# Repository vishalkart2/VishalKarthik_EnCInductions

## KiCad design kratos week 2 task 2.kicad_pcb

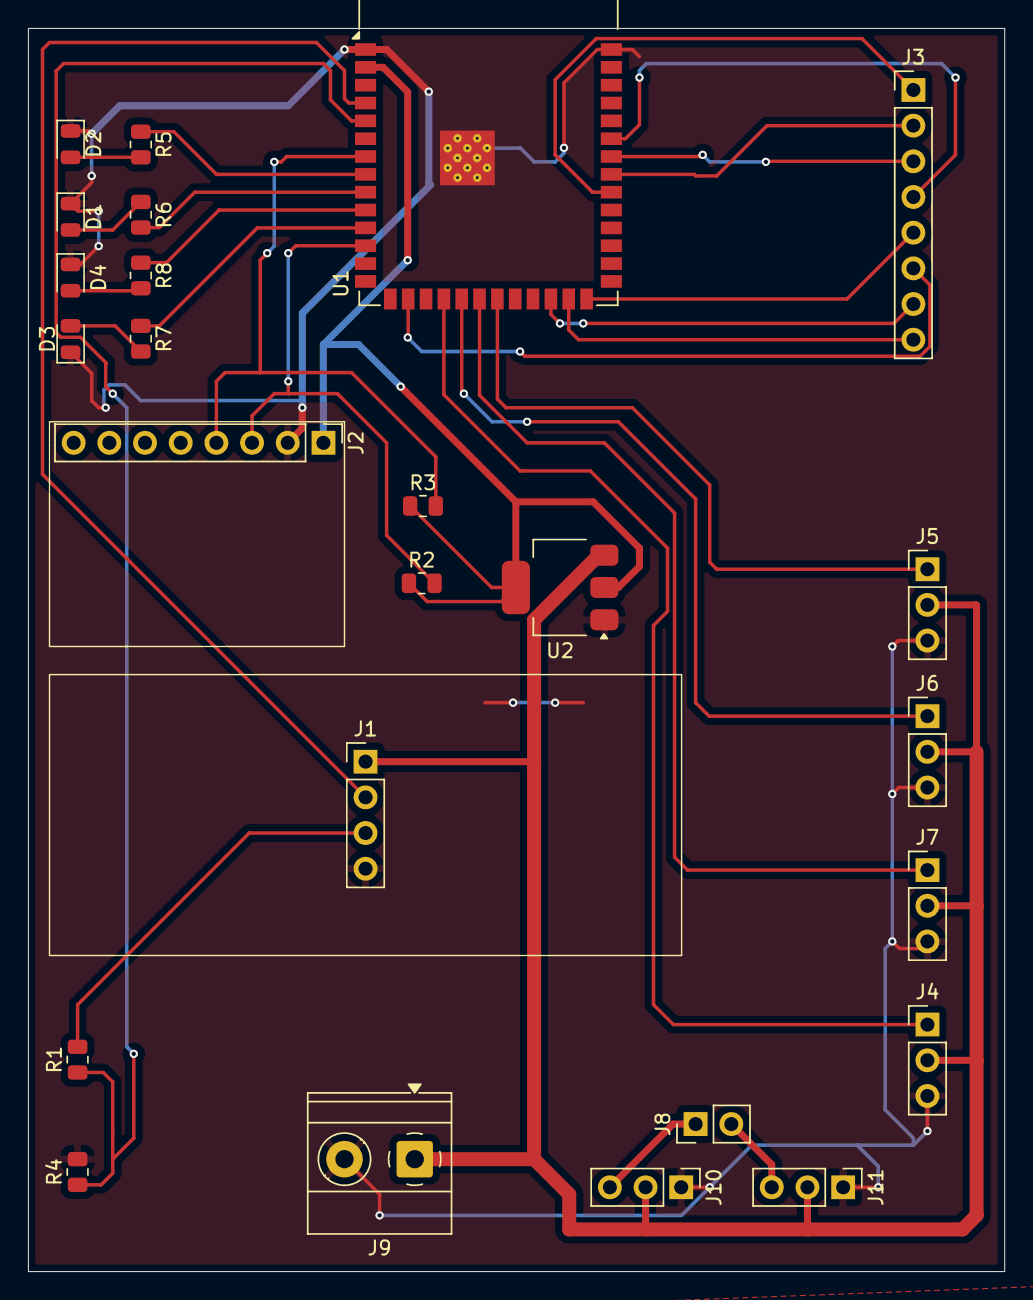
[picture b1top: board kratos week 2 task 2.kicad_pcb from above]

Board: 2 copper layers, 69.5 x 88.5 mm, 25 parts (0 on the bottom side), 30 nets.

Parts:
D1, D2, D3, D4: LED; LED_0805_2012Metric
J1: Conn_01x04; PinHeader_1x04_P2.54mm_Vertical
J2, J3: Conn_01x08; PinHeader_1x08_P2.54mm_Vertical
J4, J5, J6, J7: Conn_01x03; PinHeader_1x03_P2.54mm_Vertical
J8: Conn_01x02; PinHeader_1x02_P2.54mm_Vertical
J9: Conn_01x02; TerminalBlock_Phoenix_MKDS-1,5-2_1x02_P5.00mm_Horizontal
J10: Conn_01x03 - SWITCH 1; PinHeader_1x03_P2.54mm_Vertical
J11: Conn_01x03 - SWITCH 2; PinHeader_1x03_P2.54mm_Vertical
R1: 1000R; R_0805_2012Metric
R2, R3: 4700R; R_0805_2012Metric
R4: 2000R; R_0805_2012Metric
R5, R6, R7, R8: 220R; R_0805_2012Metric
U1: ESP32-S3-WROOM-1
U2: AMS1117-3.3; SOT-223-3_TabPin2

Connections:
+3.3V: J2.1, R2.1, R3.1, U1.2 (3V3), U2.2 (VO)
/+5V: J1.1, J4.2, J5.2, J6.2, J7.2, J9.1, J10.2, J11.2, U2.3 (VI)
/ECHO: R1.1, R4.1, U1.5 (IO5)
/GND: D1.1 (K), D2.1 (K), D3.1 (K), D4.1 (K), J1.4, J2.2, J4.3, J5.3, J6.3, J7.3, J9.2, J10.1, J11.1, R4.2, U1.1 (GND), U1.40 (GND), U1.41 (GND), U2.1 (GND)
/SCL: J2.3, R2.2, U1.12 (IO8)
/SDA: J2.4, R3.2, U1.7 (IO7)
/SER1: J4.1, U1.18 (IO10)
/SER2: J6.1, U1.19 (IO11)
/SER3: J7.1, U1.20 (IO12)
/SER4: J5.1, U1.21 (IO13)
/TRIG: J1.2, U1.4 (IO4)
unnamed: D1.2 (A), R6.1
unnamed: D2.2 (A), R5.2
unnamed: D3.2 (A), R7.2
unnamed: D4.2 (A), R8.2
unnamed: J1.3, R1.2
unnamed: J3.1, U1.32 (IO39)
unnamed: J3.2, U1.33 (IO40)
unnamed: J3.3, U1.34 (IO41)
unnamed: J3.4, U1.35 (IO42)
unnamed: J3.5, U1.26 (IO45)
unnamed: J3.6, U1.16 (IO46)
unnamed: J3.7, U1.24 (IO47)
unnamed: J3.8, U1.25 (IO48)
unnamed: J8.1, J10.3
unnamed: J8.2, J11.3
unnamed: R5.1, U1.8 (IO15)
unnamed: R6.2, U1.9 (IO16)
unnamed: R8.1, U1.10 (IO17)
unnamed: R7.1, U1.11 (IO18)
